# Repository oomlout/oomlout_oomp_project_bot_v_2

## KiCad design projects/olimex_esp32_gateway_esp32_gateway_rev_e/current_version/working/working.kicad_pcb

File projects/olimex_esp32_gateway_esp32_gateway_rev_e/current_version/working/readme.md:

# esp32_gateway
 
## summary 
* id: olimex_esp32_gateway_esp32_gateway_rev_e
* user: olimex
* name: esp32_gateway
* board: esp32_gateway_rev_e
* repo: https://github.com/OLIMEX/ESP32-GATEWAY
* src_file_repo_kicad_pcb: HARDWARE/Hardware revision E/ESP32-GATEWAY_Rev_E.kicad_pcb
* src_file_repo_kicad_pcb_link: https://github.com/OLIMEX/ESP32-GATEWAY/tree/master/HARDWARE/Hardware revision E/ESP32-GATEWAY_Rev_E.kicad_pcb

* src_file_repo_sch: HARDWARE/Hardware revision E/ESP32-GATEWAY_Rev_E.sch
* src_file_repo_sch_link: https://github.com/OLIMEX/ESP32-GATEWAY/tree/master/HARDWARE/Hardware revision E/ESP32-GATEWAY_Rev_E.sch
* full details link: https://github.com/oomlout/oomlout_oomp_project_bot_v_2/tree/main/projects/olimex_esp32_gateway_esp32_gateway_rev_e/current_version/working

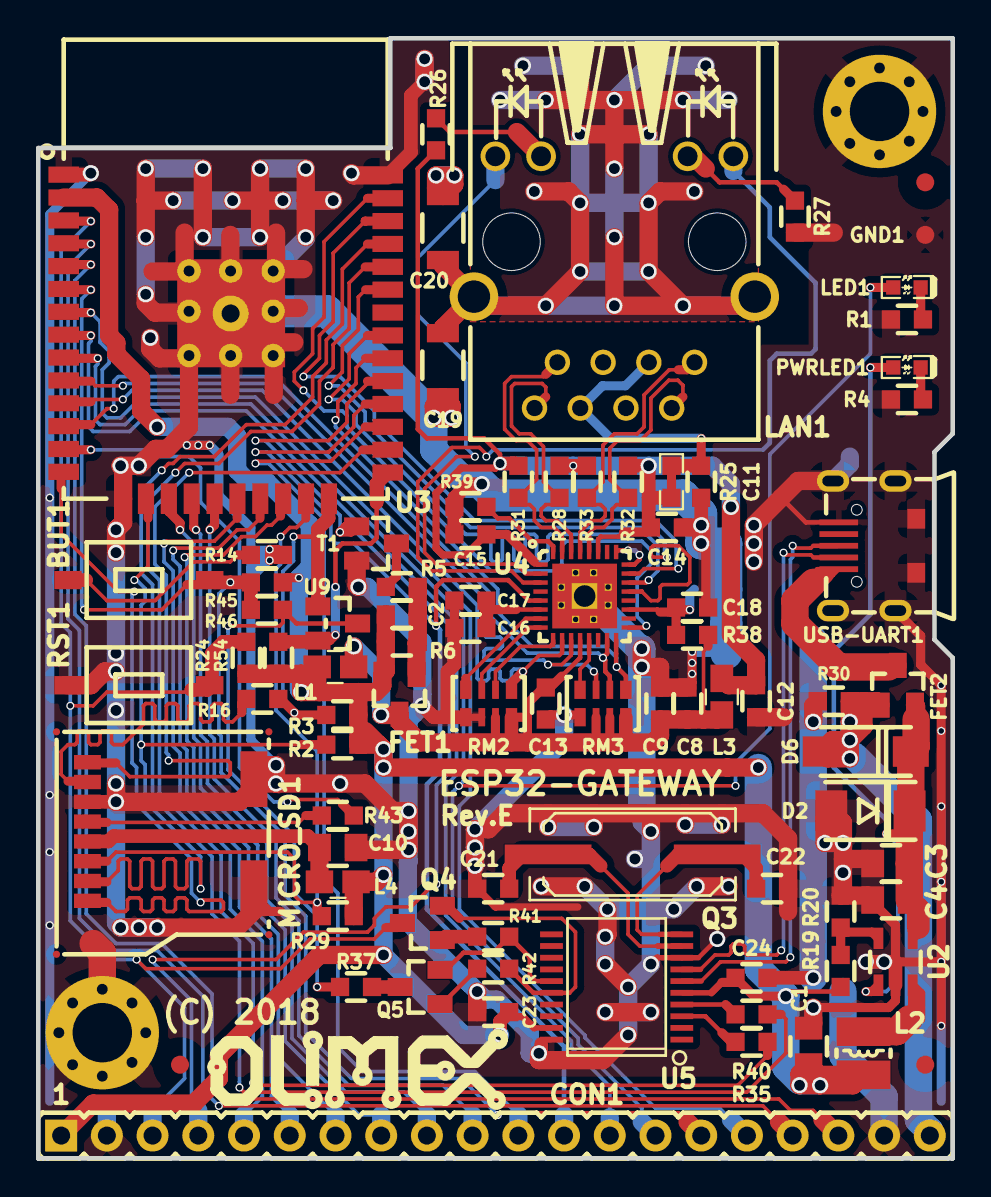
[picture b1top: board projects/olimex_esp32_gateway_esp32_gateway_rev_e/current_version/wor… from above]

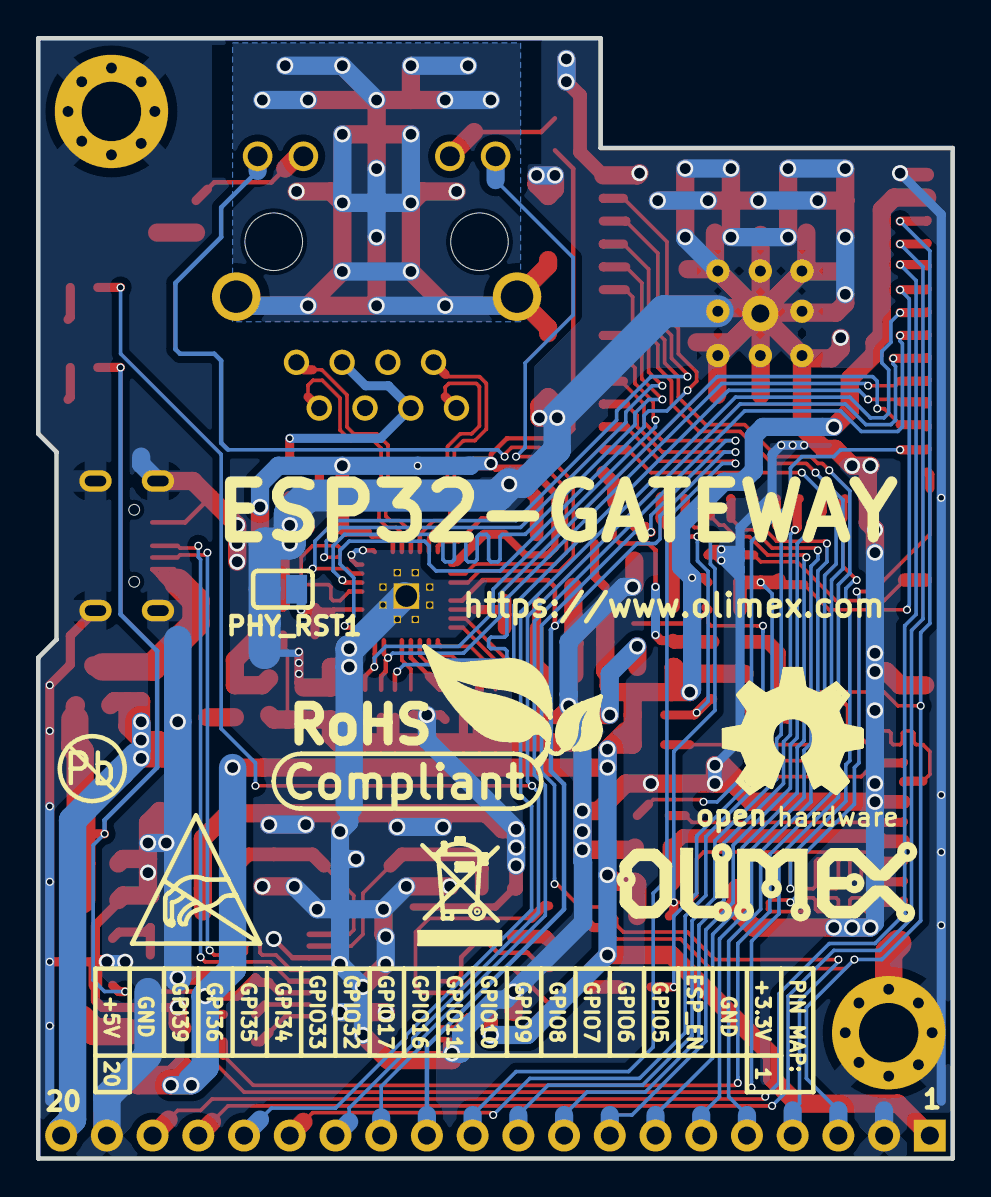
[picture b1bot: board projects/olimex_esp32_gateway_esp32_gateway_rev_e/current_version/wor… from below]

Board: 2 copper layers, 50.8 x 62.2 mm, 85 parts (3 on the bottom side), 79 nets.

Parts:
BUT1: T1107A(6x3,8x2,5MM)
C1, C3, C4, C10: 47uF/6.3V/20%/X5R/C0805; C_0805_5MIL_DWS
C2: NA/C0603; C_0603_5MIL_DWS
C8, C9, C12, C23: 22uF/6.3V/20%/X5R/C0603; C_0603_5MIL_DWS
C11, C13, C14, C15, C17, C24: 100nF/50V/20%/Y5V/C0603; C_0603_5MIL_DWS
C16: 2.2uF/6.3V/10%/X5R/C0603; C_0603_5MIL_DWS
C18: NA(10uF/6.3V/20%/X5R/C0603); C_0603_5MIL_DWS
C19: 1nF/2000V/10%/X7R/C1206; C_1206_5MIL_DWS_ISO
C20: NA(1nF/2000V/10%/X7R/C1206); C_1206_5MIL_DWS_ISO
C21, C22: 27pF/50V/5%/C0G/C0603; C_0603_5MIL_DWS
CON1: NA(NH1x20); HN1x20
D2: SMBJ6.0A(DO-214AA); DO214AA_1(K)-2(A)
D6: 1N5822/SS34/SMA; SMA-KA
FET1, FET2: WPM2015-3/TR; SOT23
GND1: TESTPAD; TESTPAD_40-ROUND
L1: NA(FB0805/600R/2A); L_0805_5MIL_DWS
L2: 2.2uH/1.5A/DCR<0.1R/CD32; CD32
L3, L4: FB0805/600R/2A; L_0805_5MIL_DWS
LAN1: RJLD-060TC1(LPJ4013EDNL); RJLBC-060TC1
LED1: LED/GREEN/0603; LED_0603_KA
MH1, MH2: Mounting_hole_Shield_3.3mm
MICRO_SD1: TFC-WXCP11-08-LF
PHY_RST1: Opened; SJ
PWRLED1: LED/RED/0603; LED_0603_KA
Q3: Q12MHz/20pF/30ppm/2P/HC-49SM(SMD); Q_49U3HMS
Q4, Q5: BC817-40(SOT23); SOT23
R1, R2, R3, R4: 2.2k/R0603; R_0603_5MIL_DWS
R5, R24, R41, R42: 1k/R0603; R_0603_5MIL_DWS
R6, R29, R30, R38, R45: 10k/R0603; R_0603_5MIL_DWS
R14, R16, R35, R37, R40: 220R/R0603; R_0603_5MIL_DWS
R19: 4.99k/1%/R0603; R_0603_5MIL_DWS
R20: 1.1k/1%/R0603; R_0603_5MIL_DWS
R25: 0R(board_mounted); 0R_0603
R26, R27: 330R/R0603; R_0603_5MIL_DWS
R28, R31, R32, R33: 49.9R/1%/R0603; R_0603_5MIL_DWS
R39: 12.1k/1%/R0603; R_0603_5MIL_DWS
R43: 10R/R0603; R_0603_5MIL_DWS
R46, R54: NA/R0603; R_0603_5MIL_DWS
RM2, RM3: RA1206_(4X0603)_4B8_2.2k; R_MATRIX_4
RST1: T1107A(6x3,8x2,5MM)
Ref**: Val**; LOGO_ANTISTATIC_1
Ref**#2: Val**; LOGO_ROHS_1
T1: DTC114YKA; SOT23
U2: SY8089AAAC(SOT23-5); SOT-23-5
U3: ESP-WROOM-32; ESP-WROOM-32_MODULE
U4: LAN8710A-EZC(QFN32); QFN32_EP(33)_5.00x5.00x0.90mm_Pitch_0.50mm
U5: CH340T(SSOP20W); SSOP-20W
U9: BAT54C(SOT23-3); SOT23-3
USB-UART1: MISB-SWMM-5B-LF(USB_MICRO); USB-MICRO_MISB-SWMM-5B_LF

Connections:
+3.3VLAN: C8.1, C9.1, C13.1, FET1.3, L1.2, L3.1, R38.2, RM2.3.1, RM2.4.1, RM3.1.2, RM3.2.2, RM3.3.2, U4.12
+3V3: C1.1, C2.1, C23.1, C24.1, CON1.1, FET1.2, L1.1, L2.2, L4.1, R2.1, R3.1, R6.1, R19.2, R24.1, R29.1, R45.1, R54.2, U3.2, U5.5, U5.19
+5V: C3.1, C4.1, D2.1, D6.1, FET2.2, PWRLED1.2, U2.1, U2.4
+5V_EXT: CON1.20, D6.2, FET2.1, R30.1
/+5V_USB: FET2.3, USB-UART1.1
/D_Com: R37.2, R46.2, U9.3
/ESP_EN: CON1.3, Q4.3, R24.2, RST1.1, U3.3
/GPI34/BUT1: BUT1.1, CON1.15, R45.2, R46.1, U3.6
/GPI35: CON1.16, U3.7
/GPI36: CON1.17, U3.4
/GPI39: CON1.18, U3.5
/GPIO0: R54.1, U3.25, U9.2
/GPIO1/U0TXD: R40.2, U3.35
/GPIO2/HS2_DATA0: R3.2, R16.1, U3.24, U9.1
/GPIO3/U0RXD: R35.2, U3.34
/GPIO4/HS2_DATA1: MICRO_SD1.8, U3.26
/GPIO5/PHY_PWR: CON1.4, T1.1, U3.29
/GPIO6/SD_CLK: CON1.5, U3.20
/GPIO7/SD_DATA0: CON1.6, U3.21
/GPIO8/SD_DATA1: CON1.7, U3.22
/GPIO9/SD_DATA2: CON1.8, U3.17
/GPIO10/SD_DATA3: CON1.9, U3.18
/GPIO11/SD_CMD: CON1.10, U3.19
/GPIO12/HS2_DATA2: MICRO_SD1.1, U3.14
/GPIO13/HS2_DATA3: MICRO_SD1.2, R2.2, U3.16
/GPIO14/HS2_CLK: R43.1, U3.13
/GPIO15/HS2_CMD: MICRO_SD1.3, R29.2, U3.23
/GPIO16: CON1.11, U3.27
/GPIO17/EMAC_CLK_OUT_180: CON1.12, U3.28, U4.5
/GPIO18/MDIO(RMII): RM3.1.1, U3.30, U4.16
/GPIO19/EMAC_TXD0(RMII): U3.31, U4.22
/GPIO21/EMAC_TX_EN(RMII): U3.33, U4.21
/GPIO22/EMAC_TXD1(RMII): U3.36, U4.23
/GPIO23/MDC(RMII): U3.37, U4.17
/GPIO25/EMAC_RXD0(RMII): RM3.3.1, U3.10, U4.11
/GPIO26/EMAC_RXD1(RMII): RM2.4.2, U3.11, U4.10
/GPIO27/EMAC_RX_CRS_DV: RM3.2.1, U3.12, U4.15
/GPIO32: CON1.13, U3.8
/GPIO33/LED: CON1.14, LED1.2, U3.9
/PHYAD0: RM3.4.1, U4.13
/PHYAD1: RM2.1.2, U4.7
/PHYAD2: RM2.2.2, U4.8
/RMIISEL: RM2.3.2, U4.9
/VDD1A-2A: C12.1, C14.1, C15.1, L3.2, R25.1, R26.1, R28.1, R31.1, R32.1, R33.1, U4.1, U4.27
/VDDCR: C16.1, C17.1, U4.6
GND: C1.2, C3.2, C4.2, C8.2, C9.2, C10.2, C11.2, C12.2, C13.2, C14.2, C15.2, C16.2, C17.2, C18.1, C19.2, C20.2, C21.2, C22.2, C23.2, C24.2, CON1.2, CON1.19, D2.2, GND1.1, MH1.GND1, MH2.GND1, MICRO_SD1.6, MICRO_SD1.SH1, MICRO_SD1.SH2, PHY_RST1.1, R1.1, R4.2, R14.2, R20.2, R27.2, R30.2, R39.2, RM2.1.1, RM2.2.1, RM3.4.2, RST1.2, T1.2, U2.2, U3.1, U3.15, U3.38, U3.39, U4.24, U4.25, U4.33, U5.8, U5.20, USB-UART1.0, USB-UART1.5
unnamed: BUT1.2, R14.1
unnamed: C2.2, FET1.1, R5.1, R6.2
unnamed: C10.1, L4.2, MICRO_SD1.4
unnamed: C11.1, LAN1.3, LAN1.6, R25.2
unnamed: C18.2, PHY_RST1.2, R38.1, U4.19
unnamed: C19.1, C20.1, LAN1.GND1, LAN1.GND2
unnamed: C21.1, Q3.1, U5.9
unnamed: C22.1, Q3.2, U5.10
unnamed: L2.1, U2.3
unnamed: LAN1.1, R33.2, U4.29
unnamed: LAN1.2, R32.2, U4.28
unnamed: LAN1.7, R31.2, U4.31
unnamed: LAN1.8, R28.2, U4.30
unnamed: LAN1.AG1, R26.2
unnamed: LAN1.AY1, U4.3
unnamed: LAN1.KG1, U4.2
unnamed: LAN1.KY1, R27.1
unnamed: LED1.1, R1.2
unnamed: MICRO_SD1.5, R43.2
unnamed: MICRO_SD1.7, R16.2
unnamed: PWRLED1.1, R4.1
unnamed: Q4.1, R41.2
unnamed: Q4.2, R42.1, U5.16
unnamed: Q5.1, R42.2
unnamed: Q5.2, R41.1, U5.15
unnamed: Q5.3, R37.1
unnamed: R5.2, T1.3
unnamed: R19.1, R20.1, U2.5
unnamed: R35.1, U5.3
unnamed: R39.1, U4.32
unnamed: R40.1, U5.4
unnamed: U5.6, USB-UART1.3
unnamed: U5.7, USB-UART1.2

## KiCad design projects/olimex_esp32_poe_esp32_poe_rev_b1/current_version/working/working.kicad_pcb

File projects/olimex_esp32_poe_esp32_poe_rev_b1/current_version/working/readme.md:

# esp32_poe
 
## summary 
* id: olimex_esp32_poe_esp32_poe_rev_b1
* user: olimex
* name: esp32_poe
* board: esp32_poe_rev_b1
* repo: https://github.com/OLIMEX/ESP32-POE
* src_file_repo_kicad_pcb: HARDWARE/ESP32-PoE-hardware-revision-B1/ESP32-PoE_Rev_B1.kicad_pcb
* src_file_repo_kicad_pcb_link: https://github.com/OLIMEX/ESP32-POE/tree/master/HARDWARE/ESP32-PoE-hardware-revision-B1/ESP32-PoE_Rev_B1.kicad_pcb

* src_file_repo_sch: HARDWARE/ESP32-PoE-hardware-revision-B1/ESP32-PoE_Rev_B1.sch
* src_file_repo_sch_link: https://github.com/OLIMEX/ESP32-POE/tree/master/HARDWARE/ESP32-PoE-hardware-revision-B1/ESP32-PoE_Rev_B1.sch
* full details link: https://github.com/oomlout/oomlout_oomp_project_bot_v_2/tree/main/projects/olimex_esp32_poe_esp32_poe_rev_b1/current_version/working

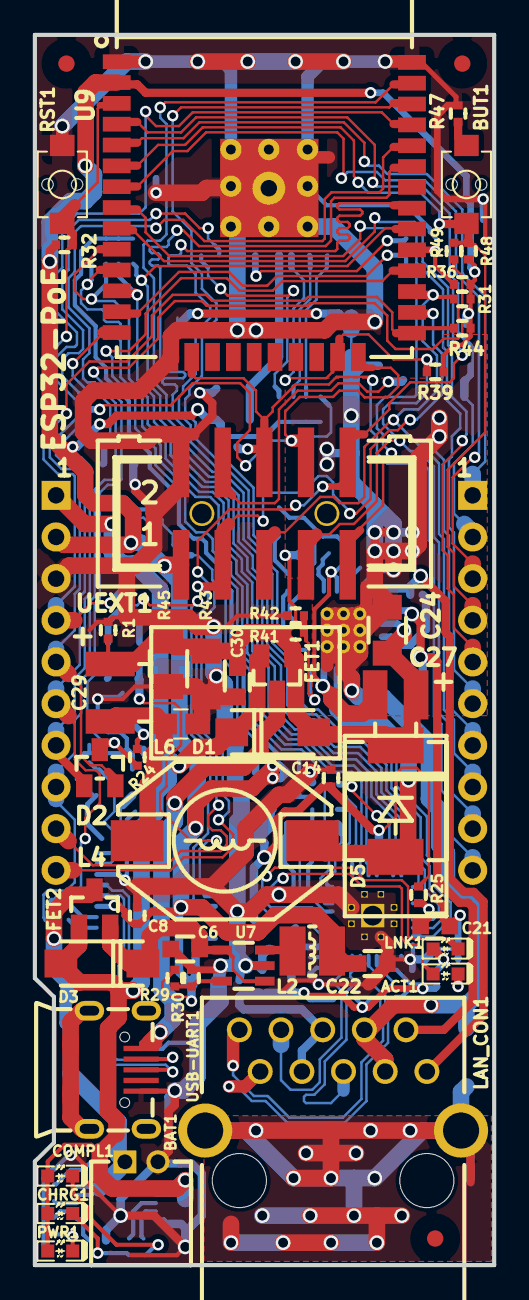
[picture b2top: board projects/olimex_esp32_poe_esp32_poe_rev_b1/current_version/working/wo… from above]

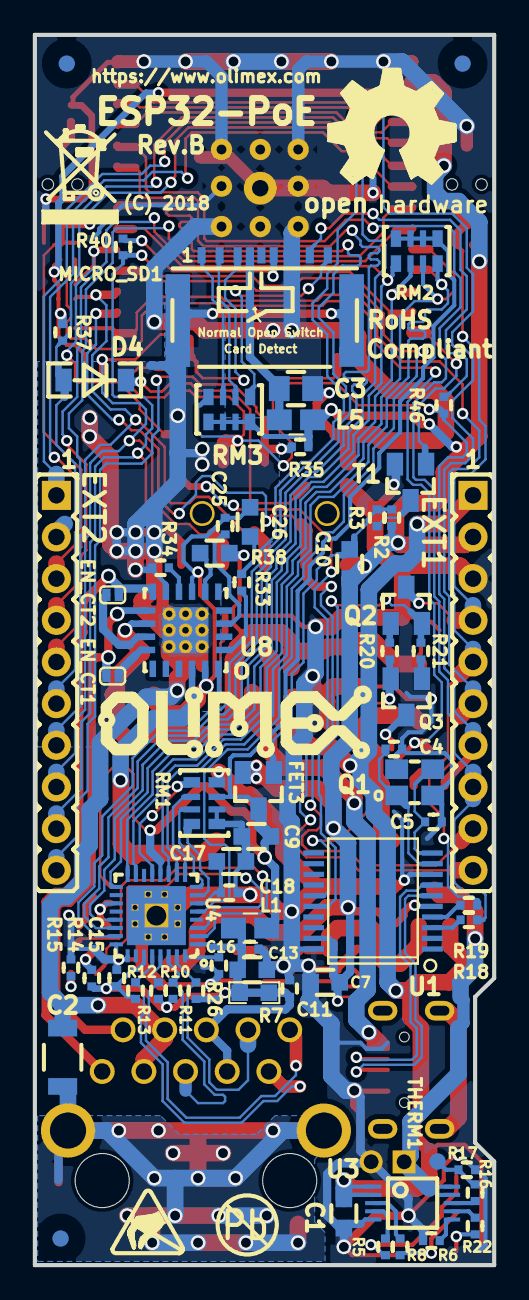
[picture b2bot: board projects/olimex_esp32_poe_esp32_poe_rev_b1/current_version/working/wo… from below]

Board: 2 copper layers, 28.0 x 75.0 mm, 119 parts (68 on the bottom side), 100 nets.

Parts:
ACT1: LED/YELLOW/0603; LED_0603_KA
BAT1: DW02R; LIPO_BAT-CON2DW02R
BUT1: IT1185AU2; IT1185AU2_V2
C1, C6, C7, C9, C10, C13, C22, C30: 22uF/6.3V/20%/X5R/C0603; C_0603_5MIL_DWS
C2: 1nF/2000V/10%/X7R/C1206; C_1206_5MIL_DWS_ISO
C3: 47uF/6.3V/20%/X5R/C0805; C_0805_5MIL_DWS
C4, C5: 27pF/50V/5%/C0G/C0402; C_0402_5MIL_DWS
C8, C11, C14, C15, C16, C18, C25: 100nF/16V/10%/X7R/C0402; C_0402_5MIL_DWS
C17: 2.2uF/6.3V/10%/X5R/C0603; C_0603_5MIL_DWS
C21: NA(10uF/6.3V/20%/X5R/C0603); C_0603_5MIL_DWS
C24: 100nF/100V/20%/C1206; C_1206_5MIL_DWS
C26: 1nF/50V/10%/X7R/C0603; C_0603_5MIL_DWS
C27: 15uF/100V/20%/RM2.5/6.3x11mm(Farnell:1281844 ); CPOL-RM2.5mm_6.3x11mm_SMD
C29: 680uF/10V/20%/105C/RM3.5/8x11.5mm; CPOL-RM3.5mm_8.0x11.5mm_SMD
CHRG1: LED/YELLOW/0603; LED_0603_KA
COMPL1: LED/GREEN/0603; LED_0603_KA
D1, D3: 1N5822/SS34/SMA; SMA-KA
D2: BAT54C(SOT23-3); SOT23-3
D4: 1N5819S4(SOD-123); SOD-123_1C-2A_KA
D5: SS510/100V/5A/0.85V/DO214AB(SMC); DO214AB(SMC)_1(K)-2(A)
EN_CT1, EN_CT2: Opened; SJ_1_SMALLER
EXT1, EXT2: NS(HN1x10); HN1x10
FET1, FET2, FET3: WPM2015-3/TR; SOT23
FID1, FID2, FID3, FID4, FID5, FID6: Fiducial; Fiducial1x3
L1, L5, L6: FB0805/600R/2A; L_0805_5MIL_DWS
L2: 2.2uH/1.5A/DCR<0.1R/CD32; CD32
L4: 33uH/2.1A/DCR=0.1R/20%/DBS135(PD3316MT330); DBS135
LAN_CON1: RJP-003TC1(LPJ4112CNL)
LNK1: LED/GREEN/0603; LED_0603_KA
MICRO_SD1: TFC-9P-1.7H(ATFFS150A01BR016); uSD(TFC-9P-1.xH(ATFFS150A01BR016))
PWR1: LED/RED/0603; LED_0603_KA
Q1: Q12MHz/20pF/10ppm/4P/3.2x2.5mm; TSX-3.2x2.5mm_GND(3)
Q2, Q3: BC817-40(SOT23); SOT23
R1, R2, R17, R25, R36, R37, R39, R48: 10k/R0402; R_0402_5MIL_DWS
R3, R16, R20, R21, R32: 1k/R0402; R_0402_5MIL_DWS
R5, R6, R8, R14, R15, R22, R31, R35: 2.2k/R0402; R_0402_5MIL_DWS
R7: 0R(board_mounted); 0R_0603
R10, R11, R12, R13, R34: 49.9R/1%/R0402; R_0402_5MIL_DWS
R18, R19, R24, R46, R47: 220R/R0402; R_0402_5MIL_DWS
R26: 12.1k/1%/R0402; R_0402_5MIL_DWS
R29: 4.99k/1%/R0402; R_0402_5MIL_DWS
R30: 1.1k/1%/R0402; R_0402_5MIL_DWS
R33: 47k/R0402; R_0402_5MIL_DWS
R38: 25.5k/1%/R0603; R_0603_5MIL_DWS
R40: 10R/R0402; R_0402_5MIL_DWS
R41: 1k/1%/R0402; R_0402_5MIL_DWS
R42: 3.01k/1%/R0402; R_0402_5MIL_DWS
R43, R45: 220R/5%/0.25W/R1206; R_1206_5MIL_DWS
R44, R49: NA/R0402; R_0402_5MIL_DWS
RM1, RM2, RM3: RA1206_(4X0603)_4B8_2.2k; R_MATRIX_4
RST1: IT1185AU2; IT1185AU2_V2
Ref**: Val**; LOGO_ANTISTATIC_SMALL_4.5mmX2.8mm
T1: DTC114YKA(SOT-23); SOT23
THERM1: TESTPAD; TESTPAD_40-ROUND
U1: CH340T(SSOP20W); SSOP-20W
U3: MCP73833(MSOP10); MSOP-10_Pitch-0.5mm_3.00x3.00x1.00mm
U4: LAN8710A-EZC(QFN32); QFN32_EP(33)_5.00x5.00x0.90mm_Pitch_0.50mm
U7: SY8089AAAC(SOT23-5); SOT-23-5
U8: Si3402-B-GM(QFN-20_5x5mm); QFN-20_5x5mm(Si3402-B-GM)
U9: ESP-WROOM-32; ESP-WROOM-32_MODULE
UEXT1: B-V-10-LF(GBH254SMT-10); GBH-254-SMT-10
USB-UART1: MISB-SWMM-5B-LF(USB_MICRO); USB-MICRO_MISB-SWMM-5B_LF

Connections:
+3.3VLAN: C9.1, C14.1, FET3.3, L1.1, R25.2, RM1.3.1, RM2.1.1, RM2.2.1, RM2.3.1, RM2.4.1, U4.12
+3V3: C7.1, C8.1, C10.1, C22.1, EXT1.2, FET3.2, L2.2, L5.1, R2.1, R29.2, R31.1, R32.1, R35.1, R36.1, R37.1, R39.1, R44.2, R48.1, RM3.1.2, RM3.2.2, RM3.3.2, RM3.4.2, U1.5, U1.19, U9.2, UEXT1.1
+5V: C1.1, CHRG1.2, COMPL1.2, D1.1, D3.2, EXT1.1, FET1.2, FET2.1, PWR1.2, U3.1, U3.2
+5VP: C24.1, C27.1, C29.1, C30.1, D1.2, D5.1, FET1.1, R1.1, R38.2, R41.1, R43.1, R45.1, U8.12
/#PG(#TE): R22.2, U3.7
/+5V_USB: FET1.3, USB-UART1.1
/D_Com: D2.3, R24.2, R49.2
/ESP_EN: EXT1.4, Q2.3, R32.2, RST1.1, U9.3
/GPI34/BUT1: BUT1.1, EXT2.4, R48.2, R49.1, U9.6
/GPI35: EXT2.3, U9.7
/GPI36/U1RXD: D4.2, EXT2.2, R37.2, U9.4
/GPI39: EXT2.1, U9.5
/GPIO0: D2.2, EXT1.5, R44.1, U9.25
/GPIO1/U0TXD: EXT1.6, R19.2, U9.35
/GPIO2/HS2_DATA0: D2.1, EXT1.7, R46.1, RM3.4.1, U9.24, UEXT1.8
/GPIO3/U0RXD: EXT1.8, R18.2, U9.34
/GPIO4/U1TXD: EXT1.9, U9.26, UEXT1.3
/GPIO5/SPI_CS: EXT1.10, R36.2, U9.29, UEXT1.10
/GPIO12/PHY_PWR: T1.1, U9.14
/GPIO13/I2C-SDA: EXT2.10, R35.2, U9.16, UEXT1.6
/GPIO14/HS2_CLK: EXT2.9, R40.1, U9.13, UEXT1.9
/GPIO15/HS2_CMD: EXT2.8, MICRO_SD1.3, R39.2, U9.23, UEXT1.7
/GPIO16/I2C-SCL: EXT2.7, R31.2, U9.27, UEXT1.5
/GPIO17/EMAC_CLK_OUT_180: U4.5, U9.28
/GPIO18/MDIO(RMII): RM2.4.2, U4.16, U9.30
/GPIO19/EMAC_TXD0(RMII): U4.22, U9.31
/GPIO21/EMAC_TX_EN(RMII): U4.21, U9.33
/GPIO22/EMAC_TXD1(RMII): U4.23, U9.36
/GPIO23/MDC(RMII): U4.17, U9.37
/GPIO25/EMAC_RXD0(RMII): RM2.2.2, U4.11, U9.10
/GPIO26/EMAC_RXD1(RMII): RM2.1.2, U4.10, U9.11
/GPIO27/EMAC_RX_CRS_DV: RM2.3.2, U4.15, U9.12
/GPIO32: EXT2.6, U9.8
/GPIO33: EXT2.5, U9.9
/STAT1: R8.2, U3.3
/STAT2: R5.2, U3.4
Earth: C2.1, C24.2, LAN_CON1.7, LAN_CON1.8, MICRO_SD1.CH1, R34.1, U8.9, U8.21
GND: BAT1.2, C1.2, C3.2, C4.2, C5.2, C6.2, C7.2, C8.2, C9.2, C11.2, C13.2, C14.2, C15.2, C16.2, C17.2, C18.2, C21.1, C22.2, C30.2, EXT1.3, L6.2, MICRO_SD1.6, Q1.3, R1.2, R6.2, R15.2, R17.2, R26.2, R30.2, R42.2, R43.2, R45.2, R47.2, RM1.1.1, RM1.2.1, RM1.4.1, RST1.2, T1.2, U1.8, U1.20, U3.5, U4.24, U4.25, U4.33, U7.2, U9.1, U9.15, U9.38, U9.39, UEXT1.2, USB-UART1.5
unnamed: ACT1.1, R15.1
unnamed: ACT1.2, U4.3
unnamed: BAT1.1, FET2.3, U3.9, U3.10
unnamed: BUT1.2, R47.1
unnamed: C2.2, LAN_CON1.0
unnamed: C3.1, L5.2, MICRO_SD1.4
unnamed: C4.1, Q1.1, U1.9
unnamed: C5.1, Q1.2, U1.10
unnamed: C6.1, D3.1, FET2.2, U7.1, U7.4
unnamed: C10.2, FET3.1, R2.2, R3.1
unnamed: C11.1, LAN_CON1.4, LAN_CON1.5, R7.2
unnamed: C13.1, C15.1, C16.1, L1.2, R7.1, R10.1, R11.1, R12.1, R13.1, R14.1, U4.1, U4.27
unnamed: C17.1, C18.1, U4.6
unnamed: C21.2, R25.1, U4.19
unnamed: C25.1, U8.3
unnamed: C25.2, C26.2, C27.2, U8.7, U8.19
unnamed: C26.1, R33.1
unnamed: C29.2, L4.2, L6.1
unnamed: CHRG1.1, R8.1
unnamed: COMPL1.1, R5.1
unnamed: D4.1, UEXT1.4
unnamed: D5.2, L4.1, U8.18
unnamed: EN_CT1.1, U8.14
unnamed: EN_CT2.1, U8.13
unnamed: L2.1, U7.3
unnamed: LAN_CON1.1, R13.2, U4.29
unnamed: LAN_CON1.2, R12.2, U4.28
unnamed: LAN_CON1.3, R11.2, U4.31
unnamed: LAN_CON1.6, R10.2, U4.30
unnamed: LNK1.1, U4.2
unnamed: LNK1.2, R14.2
unnamed: MICRO_SD1.1, RM3.3.1
unnamed: MICRO_SD1.2, RM3.2.1
unnamed: MICRO_SD1.5, R40.2
unnamed: MICRO_SD1.7, R46.2
unnamed: MICRO_SD1.8, RM3.1.1
unnamed: PWR1.1, R22.1
unnamed: Q2.1, R20.2
unnamed: Q2.2, R21.1, U1.16
unnamed: Q3.1, R21.2
unnamed: Q3.2, R20.1, U1.15
unnamed: Q3.3, R24.1
unnamed: R3.2, T1.3
unnamed: R6.1, U3.6
unnamed: R16.1, U3.8
unnamed: R16.2, R17.1, THERM1.1
unnamed: R18.1, U1.3
unnamed: R19.1, U1.4
unnamed: R26.1, U4.32
unnamed: R29.1, R30.1, U7.5
unnamed: R33.2, U8.1
unnamed: R34.2, U8.8
unnamed: R38.1, U8.6
unnamed: R41.2, R42.1, U8.20
unnamed: RM1.1.2, U4.7
unnamed: RM1.2.2, U4.8
unnamed: RM1.3.2, U4.9
unnamed: RM1.4.2, U4.13
unnamed: U1.6, USB-UART1.3
unnamed: U1.7, USB-UART1.2
Spare1: EN_CT1.2, LAN_CON1.9, U8.11
Spare2: EN_CT2.2, LAN_CON1.10, U8.10

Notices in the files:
projects/olimex_esp32_gateway_esp32_gateway_rev_e/current_version/working/working.kicad_pcb:
(C) 2018
